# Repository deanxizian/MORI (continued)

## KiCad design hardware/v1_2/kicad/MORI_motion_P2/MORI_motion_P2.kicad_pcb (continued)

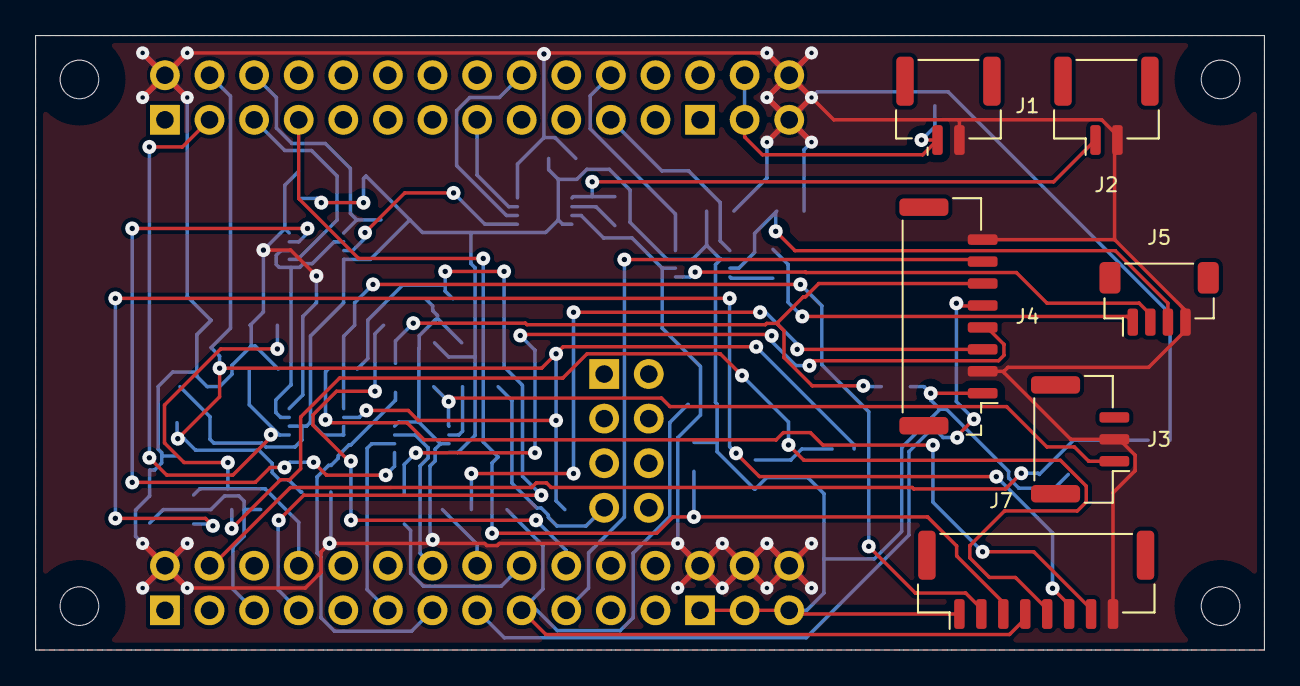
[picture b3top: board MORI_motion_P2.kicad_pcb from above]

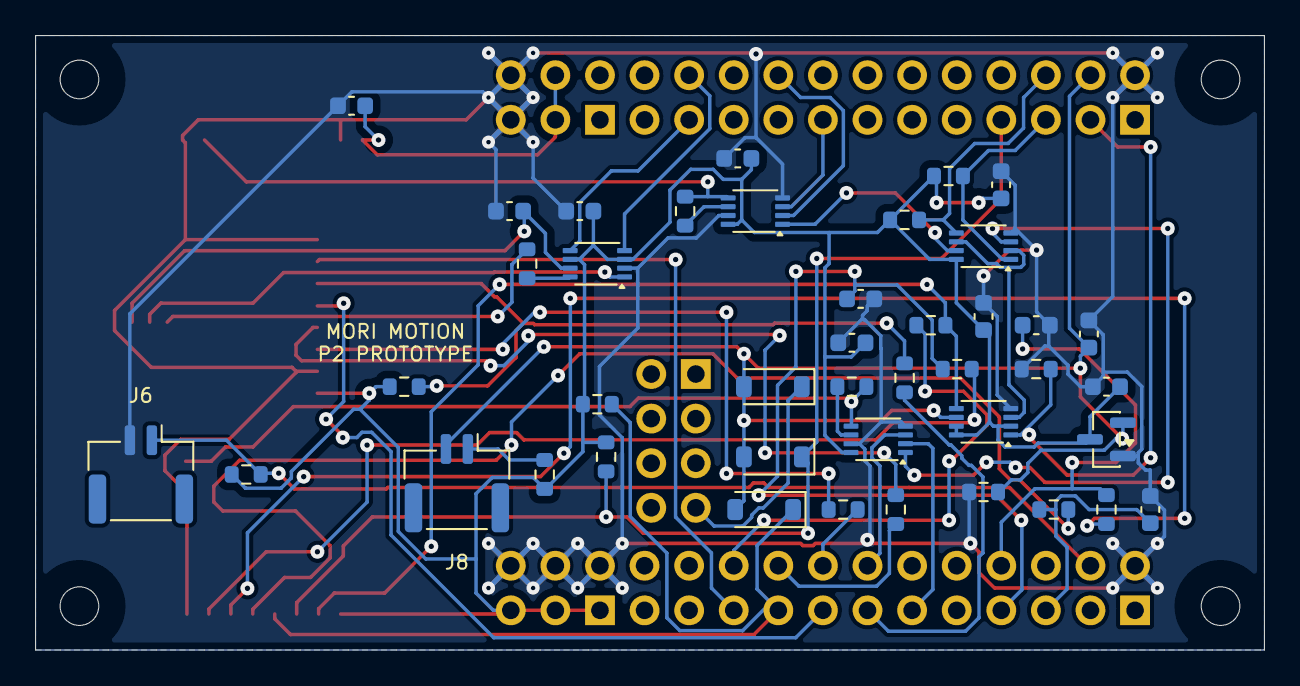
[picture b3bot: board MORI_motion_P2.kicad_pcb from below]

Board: 2 copper layers, 70.0 x 35.0 mm, 53 parts (42 on the bottom side), 45 nets.

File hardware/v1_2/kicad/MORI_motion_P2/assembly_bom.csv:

ref,value,footprint,source,note
U100,WeAct STM32F412RET6 64Pin V1.1,MORI_Custom:WeAct_F4_64Pin_V11,https://github.com/WeActStudio/WeActStudio.STM32F4_64Pin_CoreBoard,"A=P1 B=P2 C=P3 D=P4 E=P5. Complete module footprint; manufacturer drawing, NOT measured. P5 SWD accessible from module top; E7 reset tap only."
J1,MOTION 5V IN,MORI_Custom:JST_GH_BM02B-GHS-TBT_1x02-1MP_P1.25mm_Vertical__P2_J1,,Pin numbers are PCB connector numbers; harness mating view must be continuity checked.
J2,S288 DATA ONLY,Connector_JST:JST_GH_BM02B-GHS-TBT_1x02-1MP_P1.25mm_Vertical,,Pin numbers are PCB connector numbers; harness mating view must be continuity checked.
J3,HEAD DATA ONLY,Connector_JST:JST_GH_BM03B-GHS-TBT_1x03-1MP_P1.25mm_Vertical,,Pin numbers are PCB connector numbers; harness mating view must be continuity checked.
J4,BODY IMU SPI,MORI_Custom:JST_GH_BM08B-GHS-TBT_1x08-1MP_P1.25mm_Vertical__P2_J4,,Pin numbers are PCB connector numbers; harness mating view must be continuity checked.
J5,CAM J11 MATCH,Connector_JST:JST_SH_BM04B-SRSS-TB_1x04-1MP_P1.00mm_Vertical,,Pin numbers are PCB connector numbers; harness mating view must be continuity checked.
J6,USER BUTTON,Connector_JST:JST_GH_BM02B-GHS-TBT_1x02-1MP_P1.25mm_Vertical,,Pin numbers are PCB connector numbers; harness mating view must be continuity checked.
J7,POWER CONTROL,Connector_JST:JST_GH_BM08B-GHS-TBT_1x08-1MP_P1.25mm_Vertical,,Pin numbers are PCB connector numbers; harness mating view must be continuity checked.
J8,LATCHED ENABLE LOOP,Connector_JST:JST_GH_BM02B-GHS-TBT_1x02-1MP_P1.25mm_Vertical,,Pin numbers are PCB connector numbers; harness mating view must be continuity checked.
U1,SN74LVC2G125DCUR,MORI_Custom:TI_DCU0008A_0p85x0p30,https://www.ti.com/lit/ds/symlink/sn74lvc2g125.pdf,Ioff; bus input 0..5.5V. External actuator VIH/VOH not yet verified. Default no transmission.
U2,SN74LVC2G125DCUR,MORI_Custom:TI_DCU0008A_0p85x0p30,https://www.ti.com/lit/ds/symlink/sn74lvc2g125.pdf,Ioff; bus input 0..5.5V. External actuator VIH/VOH not yet verified. Default no transmission.
U3,SN74LVC2G32DCUR,MORI_Custom:TI_DCU0008A_0p85x0p30,https://www.ti.com/lit/ds/symlink/sn74lvc2g32.pdf,
U4,TXU0202DCUR,MORI_Custom:TI_DCU0008A_0p85x0p30,https://www.ti.com/lit/ds/symlink/txu0202.pdf,"VCC isolation and Ioff; J11.3 powers only translator B rail, never feeds motion regulator."
U5,SN74LVC1G74DCUR,MORI_Custom:TI_DCU0008A_0p85x0p30,https://www.ti.com/lit/ds/symlink/sn74lvc1g74.pdf,Physical loop + supervisor + faults clear latch; only a new explicit ARM rising edge re-enables.
U6,TLV803EA29DBZR,Package_TO_SOT_SMD:SOT-23,https://www.ti.com/lit/ds/symlink/tlv803e.pdf,"2.93V threshold,200ms reset; exact non-R/non-V pinout."
D1,"BAT54H,115",Diode_SMD:D_SOD-123,,"Cathode pin1; pulls latch clear low, does not reset MCU on ordinary disable."
D2,"BAT54H,115",Diode_SMD:D_SOD-123,,"Cathode pin1; pulls latch clear low, does not reset MCU on ordinary disable."
D3,"BAT54H,115",Diode_SMD:D_SOD-123,,"Cathode pin1; pulls latch clear low, does not reset MCU on ordinary disable."
R1,68,Resistor_SMD:R_0603_1608Metric,,
R2,68,Resistor_SMD:R_0603_1608Metric,,
R3,10k,Resistor_SMD:R_0603_1608Metric,,
R4,10k,Resistor_SMD:R_0603_1608Metric,,
R5,10k,Resistor_SMD:R_0603_1608Metric,,
R6,1k,Resistor_SMD:R_0603_1608Metric,,
R7,10k,Resistor_SMD:R_0603_1608Metric,,
R8,10k,Resistor_SMD:R_0603_1608Metric,,
R9,47,Resistor_SMD:R_0603_1608Metric,,
R10,33,Resistor_SMD:R_0603_1608Metric,,
R11,33,Resistor_SMD:R_0603_1608Metric,,
R12,33,Resistor_SMD:R_0603_1608Metric,,
R13,10k,Resistor_SMD:R_0603_1608Metric,,
R14,1k,Resistor_SMD:R_0603_1608Metric,,
R15,1k,Resistor_SMD:R_0603_1608Metric,,
R16,1k,Resistor_SMD:R_0603_1608Metric,,
R17,10k,Resistor_SMD:R_0603_1608Metric,,
R18,10k,Resistor_SMD:R_0603_1608Metric,,
R19,1k,Resistor_SMD:R_0603_1608Metric,,
C1,100n,Capacitor_SMD:C_0603_1608Metric,,
C2,100n,Capacitor_SMD:C_0603_1608Metric,,
C3,100n,Capacitor_SMD:C_0603_1608Metric,,
C4,100n,Capacitor_SMD:C_0603_1608Metric,,
C5,100n,Capacitor_SMD:C_0603_1608Metric,,
C6,100n,Capacitor_SMD:C_0603_1608Metric,,
C7,100n,Capacitor_SMD:C_0603_1608Metric,,
C8,10u,Capacitor_SMD:C_0603_1608Metric,,
C9,10n,Capacitor_SMD:C_0603_1608Metric,,
C10,10n,Capacitor_SMD:C_0603_1608Metric,,
C11,10n,Capacitor_SMD:C_0603_1608Metric,,
C12,100n,Capacitor_SMD:C_0603_1608Metric,,
H1,M2 clearance,MountingHole:MountingHole_2.2mm_M2,,
H2,M2 clearance,MountingHole:MountingHole_2.2mm_M2,,
H3,M2 clearance,MountingHole:MountingHole_2.2mm_M2,,
H4,M2 clearance,MountingHole:MountingHole_2.2mm_M2,,
